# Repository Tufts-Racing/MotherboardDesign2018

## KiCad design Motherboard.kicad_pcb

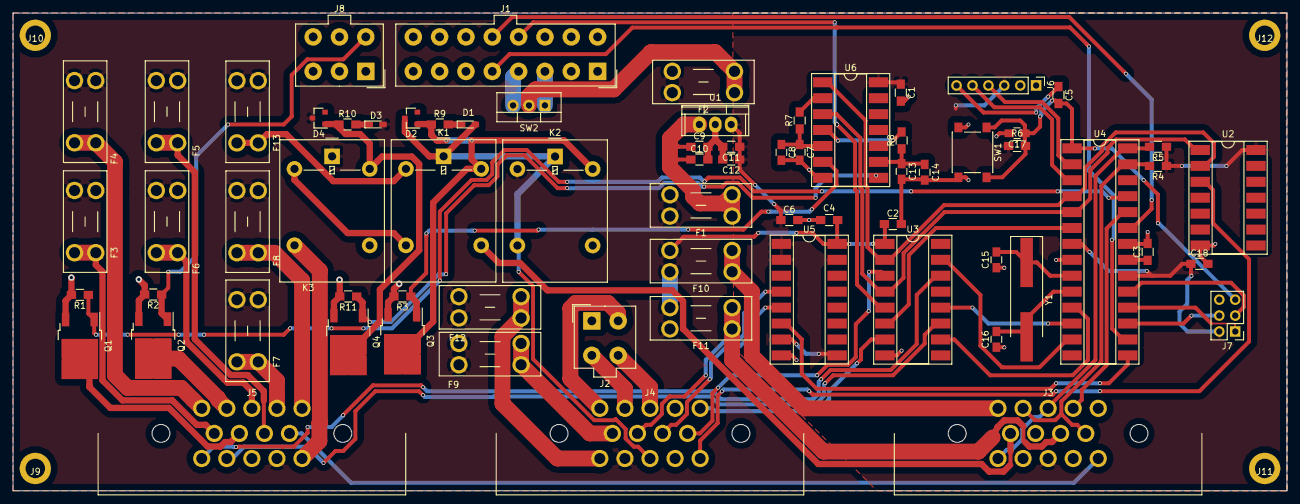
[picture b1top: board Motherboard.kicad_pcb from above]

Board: 2 copper layers, 203.2 x 76.2 mm, 74 parts (0 on the bottom side), 70 nets.

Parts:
C1, C2, C4, C5, C6: 1u; R_0805_HandSoldering
C3: .1u; R_0805_HandSoldering
C7, C8, C13, C14, C15, C16, C17: C; C_0805_HandSoldering
C9, C10, C11, C12, C18: C; R_0805_HandSoldering
D1: IMD_OK; LED_0603_HandSoldering
D2: IMD_FLYBACK; D_SOT-23_ANK
D3: BMS_OK; LED_0603_HandSoldering
D4: BMS_FLYBACK; D_SOT-23_ANK
F1: 5V_FUSE; BladeFuse-Mini_Keystone_3568
F2: BMS_FUSE; BladeFuse-Mini_Keystone_3568
F3: RTDS_FUSE; BladeFuse-Mini_Keystone_3568
F4: BATTERY_FAN_FUSE; BladeFuse-Mini_Keystone_3568
F5: BRK_LIGHT_FUSE; BladeFuse-Mini_Keystone_3568
F6: RADIATOR_FAN_FUSE; BladeFuse-Mini_Keystone_3568
F7: PUMP_FUSE; BladeFuse-Mini_Keystone_3568
F8: LAP_TIMER_FUSE; BladeFuse-Mini_Keystone_3568
F9: SEVCON_FUSE; BladeFuse-Mini_Keystone_3568
F10: WHEEL_FUSE; BladeFuse-Mini_Keystone_3568
F11: DAQ_FUSE; BladeFuse-Mini_Keystone_3568
F12: IMD_FUSE; BladeFuse-Mini_Keystone_3568
F13: SD_FUSE; BladeFuse-Mini_Keystone_3568
J1: Conn_01x16_Male; Molex_MiniFit-JR-5556-16A_2x08x4.20mm_Straight
J2: Conn_01x04_Male; Molex_MiniFit-JR-5556-04A_2x02x4.20mm_Straight
J3, J4, J5: Conn_01x14_Male; AMP14
J6: FTDI; Pin_Header_Straight_1x06_Pitch2.54mm
J7: ICSP; Pin_Header_Straight_2x03_Pitch2.54mm
J8: Conn_01x06_Male; Molex_MiniFit-JR-5556-06A_2x03x4.20mm_Straight
J9, J10, J11, J12: Conn_01x01; MountingPadM3
K1: IMD_RELAY; Relay_SPDT_OMRON-G5LE-1
K2: IMD_LATCH; Relay_SPDT_OMRON-G5LE-1
K3: BMS_RELAY; Relay_SPDT_OMRON-G5LE-1
Q1, Q2, Q3, Q4: Q_NMOS_GDS; TO-252-2
R1, R2, R3, R4, R5, R6, R11: 10k; R_0805_HandSoldering
R7, R8, R9, R10: R; R_0805_HandSoldering
SW1: SW_Push; SW_SPST_PTS645
SW2: SW_SPDT; TO-220-3_Vertical
U1: LM7805_TO220; TO-220
U2: 74HC00; DIP-14_W8.89mm_SMDSocket_LongPads
U3: CD4050; DIP-16_W8.89mm_SMDSocket_LongPads
U4: ATMEGA328P-PU; DIP-28_W8.89mm_SMDSocket_LongPads
U5: CD40109; DIP-16_W8.89mm_SMDSocket_LongPads
U6: 74HC14; DIP-14_W8.89mm_SMDSocket_LongPads
Y1: Crystal; Crystal_SMD_HC49-SD_HandSoldering

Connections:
+5V: C1.1, C6.1, C11.1, C12.1, C18.1, J3.12, J6.3, J7.2, R4.1, R5.1, R6.1, U1.3, U2.14, U4.7, U4.20, U5.1, U5.2, U5.7, U5.9, U5.15, U6.14
+12V: C2.1, C4.1, D3.2, D4.1, F1.2, F2.2, F3.2, F4.2, F5.2, F6.2, F7.2, F8.2, F9.2, F10.2, F11.2, F12.2, F13.2, J4.11, J5.13, K2.2, K3.1, U3.1, U5.16
/BATT_FAN+: F4.1, J5.1
/BATT_FAN-: J5.2, Q2.2
/BMS_FLT: J1.12, U3.5
/BOTS: J5.11, U3.11
/BRK_LIGHT+: F5.1, J5.8
/BRK_SW: J3.14, J5.9
/CHARGER_SD: J4.14, U2.3
/CONTACT_REQ: J1.5, U4.16
/FAN_PWM: J8.4, Q2.1, R2.1
/IMD_FLT: J4.9, U3.3
/IMD_FLT_12V_LED_H: J3.6, K1.4
/IMD_RST-: D1.2, D2.1, J4.12, K1.1, K2.1, K2.3
/K1: J2.2, J4.1
/K2: J2.3, J4.2
/K3: J2.4, J4.3
/LAP_TIMER+: F8.1, J5.5
/Logic/BOTS: U3.12, U4.12
/Logic/COCKPIT_SW: U3.10, U4.11
/Logic/RST: C5.2, C17.1, J7.5, R6.2, SW1.1, U4.1
/Logic/RTDS: Q1.1, R1.1, U4.25
/Logic/RX: J6.4, U4.2
/Logic/SEVCON_FLT: U3.6, U4.6
/Logic/SEVCON_REV: U4.15, U5.6
/Logic/TSMS: U3.15, U4.13
/Logic/TX: J6.5, U4.3
/PUMP+: F7.1, J5.4
/RAD_FAN+: F6.1, J5.3
/RTDS+: F3.1, J5.6
/RTDS-: J5.7, Q1.2
/SCL: J3.3, J3.10, R5.2, U4.28
/SDA: J3.2, J3.9, R4.2, U4.27
/SD_CKT-: J5.14, K3.3
/SEVCON_FLT: J4.5, U3.7
/SEVCON_FWD: J4.7, U5.4
/SEVCON_REV: J4.8, U5.5
/SOC: J1.13, U4.23
/START_INPUT: J3.4, U4.24
/ShutdownCircuit/BMS_FLT_5V_L: Q4.1, R11.1, U6.8
/ShutdownCircuit/IMD_FLT_5V_L: Q3.1, R3.1, U6.6
/SignalDelay/A1: U2.2, U3.2, U4.4, U6.1
/SignalDelay/A2: U2.1, U3.4, U4.5, U6.3
/TSMS: J5.10, U3.14
GND: C1.2, C2.2, C3.2, C4.2, C6.2, C7.2, C8.2, C9.2, C10.2, C11.2, C12.2, C13.2, C14.2, C15.1, C16.1, C17.2, C18.2, J1.1, J1.9, J3.5, J3.7, J3.11, J4.4, J4.13, J6.1, J6.2, J7.6, J8.1, Q1.3, Q2.3, Q3.3, Q4.3, R1.2, R2.2, R3.2, R11.2, SW1.2, U1.2, U2.7, U3.8, U4.8, U4.22, U5.8, U6.7
unnamed: C3.1, U4.21
unnamed: C5.1, J6.6
unnamed: C7.1, C8.1, R7.1, U6.5
unnamed: C9.1, C10.1, F1.1, U1.1
unnamed: C13.1, C14.1, R8.1, U6.9
unnamed: C15.2, U4.9, Y1.1
unnamed: C16.2, U4.10, Y1.2
unnamed: D1.1, R9.2
unnamed: D2.2, K1.5, K2.5, Q3.2, R9.1
unnamed: D3.1, R10.2
unnamed: D4.2, K3.5, Q4.2, R10.1
unnamed: F2.1, SW2.2
unnamed: F9.1, J4.6
unnamed: F10.1, J3.1
unnamed: F11.1, J3.8
unnamed: F12.1, J4.10
unnamed: F13.1, K1.2
unnamed: J1.3, SW2.1
unnamed: J1.4, SW2.3
unnamed: J7.1, U4.18
unnamed: J7.3, U4.19
unnamed: J7.4, U4.17
unnamed: K1.3, K3.2
unnamed: R7.2, U6.2
unnamed: R8.2, U6.4

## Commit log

2017-11-09 added mobo design
2017-11-09 added gitignore
2017-11-09 added library configuration to point to libraries repo in sister directory
2017-11-09 updated library paths to reflect remote directory names
2017-11-18 added noel's revisions
2017-11-19 added charger sd logic
2017-11-25 added most footprint associations
2017-11-27 beginning board design
2017-11-29 working on bms connectors
2017-12-06 stuff
2017-12-11 beginning floorplan
2018-01-22 winter break changes
2018-02-14 finished routing
2018-05-02 final design competition 2018
